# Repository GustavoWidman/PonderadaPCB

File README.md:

# PonderadaPCB

## Gustavo Wagon Widman

Esse repositório contém o código fonte da PCB desenvolvida para uma atividade ponderada. A atividade tem por objetivo desenvolver uma placa de circuito impresso capaz de receber um Raspberry Pi Pico W encaixado utilizando um dispositivo conector, além de um hardware para acionar uma interface de potência (relé e transistor), um dispositivo sinalizador (LED ou Buzzer) e um dispositivo de entrada (analógico ou digital). O projeto foi desenvolvido utilizando o software KiCad.

## Descrição do Projeto

O projeto foi desenvolvido utilizando o software KiCad. A placa de circuito impresso foi desenvolvida para ser utilizada em conjunto com um Raspberry Pi Pico W. A placa possui um conector para encaixe do Raspberry Pi Pico W, e diversos pequenos circuitos:

- Switch para interface de entrada: O switch é conectado ao pino GP22 do Raspberry Pi Pico W e pode ser utilizado para acionar um evento no software rodando no Raspberry Pi Pico W.
- LED para interface de saída: O LED é conectado ao pino GP17 do Raspberry Pi Pico W e pode ser controlado pelo software rodando no Raspberry Pi Pico W.
- Transistor conectado a um buzzer: O transistor é conectado ao pino GP16 do Raspberry Pi Pico W e pode ser utilizado para ativar e desativar um buzzer.

## Estrutura do Projeto

```bash
.
├── README.md
├── assets
│   ├── 3D.png
│   ├── PCB.png
│   └── Schematic.png
└── src
    ├── PonderadaPCB.kicad_pcb
    ├── PonderadaPCB.kicad_pro
    ├── PonderadaPCB.kicad_sch
    └── gerber
        ├── PonderadaPCB-B_Cu.gbr
        ├── PonderadaPCB-B_Mask.gbr
        ├── PonderadaPCB-B_Paste.gbr
        ├── PonderadaPCB-B_Silkscreen.gbr
        ├── PonderadaPCB-Edge_Cuts.gbr
        ├── PonderadaPCB-F_Cu.gbr
        ├── PonderadaPCB-F_Mask.gbr
        ├── PonderadaPCB-F_Paste.gbr
        ├── PonderadaPCB-F_Silkscreen.gbr
        └── PonderadaPCB-job.gbrjob
```

A pasta `assets` contém imagens do projeto (demonstradas neste arquivo README). A pasta `src` contém os arquivos do projeto KiCad, incluindo o esquemático, a PCB e os arquivos gerber para fabricação da placa de circuito impresso, que estão localizados na pasta `gerber` (dentro da pasta `src`).

## Imagens do Projeto

### Esquemático

### PCB

### 3D

## Lista de Materiais

| Componente          | Footprint                                         | Quantidade |
| ------------------- | ------------------------------------------------- | ---------- |
| Raspberry Pi Pico W | RPi_Pico_SMD_TH                                   | 1          |
| Switch              | SW_Slide-03_Wuerth-WS-SLTV_10x2.5x6.4_P2.54mm     | 1          |
| LED                 | LED_D5.0mm                                        | 1          |
| Transistor          | TO-92_Inline                                      | 1          |
| Buzzer              | Buzzer_15x7.5RM7.6                                | 1          |
| Resistor 220 Ohm    | R_Axial_DIN0207_L6.3mm_D2.5mm_P15.24mm_Horizontal | 1          |
| Resistor 10k Ohm    | R_Axial_DIN0207_L6.3mm_D2.5mm_P15.24mm_Horizontal | 1          |

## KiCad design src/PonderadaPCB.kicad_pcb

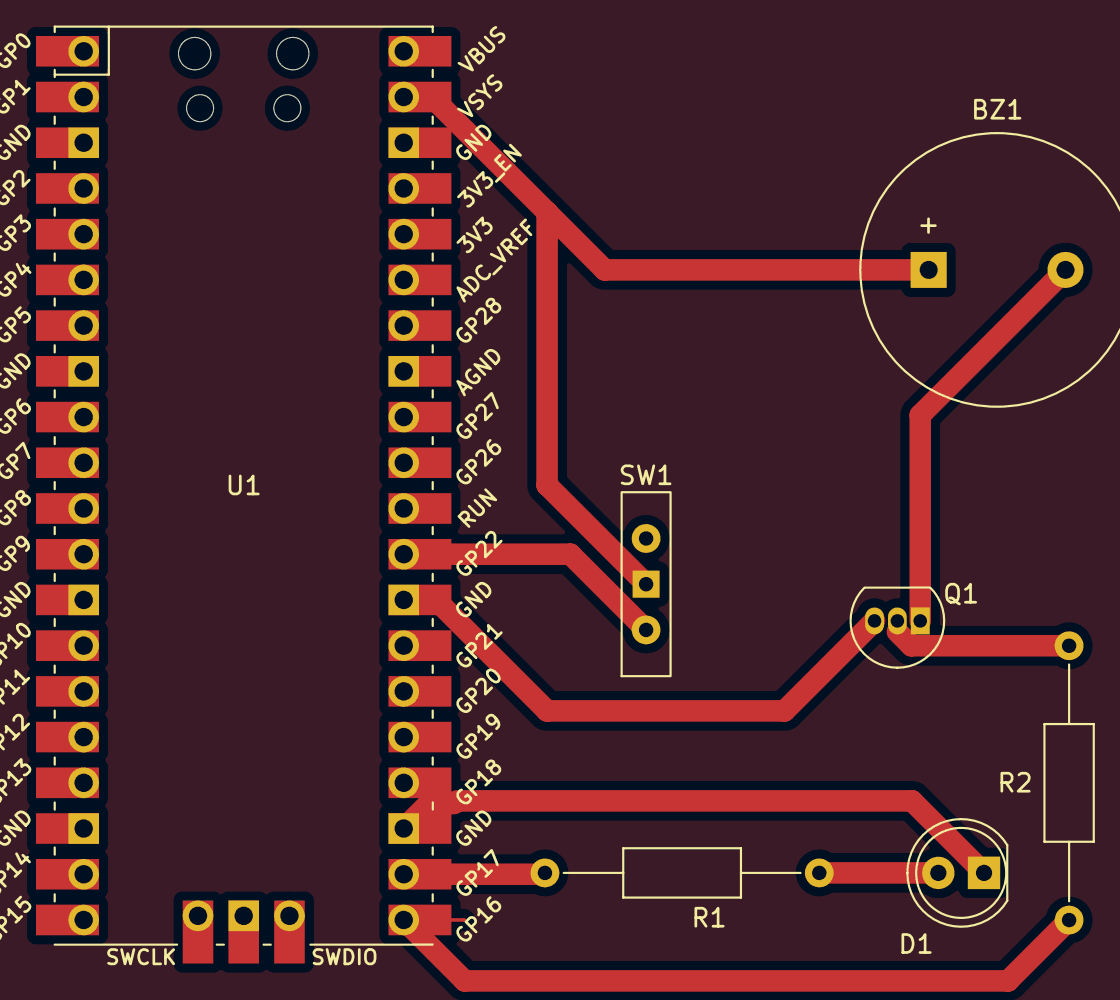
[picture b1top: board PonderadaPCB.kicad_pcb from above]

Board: 2 copper layers, 7 parts (0 on the bottom side), 8 nets.

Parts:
BZ1: Buzzer; Buzzer_15x7.5RM7.6
D1: LED; LED_D5.0mm
Q1: BC337; TO-92_Inline
R1: 220; R_Axial_DIN0207_L6.3mm_D2.5mm_P15.24mm_Horizontal
R2: 10K; R_Axial_DIN0207_L6.3mm_D2.5mm_P15.24mm_Horizontal
SW1: SW_Wuerth_450301014042; SW_Slide-03_Wuerth-WS-SLTV_10x2.5x6.4_P2.54mm
U1: Pico; RPi_Pico_SMD_TH

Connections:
GND (Buzzer): Q1.3 (E), U1.27 (GPIO21), U1.28 (GND)
GND (LED): D1.1 (K), U1.23 (GND), U1.24 (GPIO18)
GP16 (Buzzer): R2.1, U1.21 (GPIO16)
GP17 (LED): R1.1, U1.22 (GPIO17)
GP22 (Switch): SW1.2 (C), U1.29 (GPIO22)
unnamed: D1.2 (A), R1.2
unnamed: BZ1.2 (-), Q1.1 (C), Q1.2 (B), R2.2
VCC: BZ1.1 (+), SW1.1 (B), U1.38 (GND), U1.39 (VSYS)

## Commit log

2024-04-01 Mudar modelo do Switch
2024-04-01 Consertar circuito de Switch
2024-04-01 Alterar estilizacao da estrutura do projeto
2024-05-21 Create LICENSE
